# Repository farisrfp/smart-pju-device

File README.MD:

# **SMART PJU X-CAMP**

_Created by [Faris Rafi](https://www.linkedin.com/in/farisrafp/), last updated on 20 May 2023_

## **About SMART PJU**

This Smart PJU is a continuation of X-Bright with the addition of new features such as communication using LoRa, the use of new sensors, and the use of new modules. This Smart PJU also uses the concept of IoT (Internet of Things) which allows users to control this street lamp through the dashboard provided.

### **Wiring Diagram**

### **Hardware**

|               Controller V2               |
| :---------------------------------------: |
|  |

|            Power V2             |
| :-----------------------------: |
|  |

Documentation can be seen [here](./hardware/)

### **Firmware**

Here is the sensor diagram and pinout used on Controller V2.

Documentation can be seen [here](./firmware/)

## **Contact**

If you have any questions, please contact Faris, the product's designer, by E-mail.

Email : farisrafp@gmail.com

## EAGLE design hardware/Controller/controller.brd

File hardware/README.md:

# **Hardware Documentation**

## **BOM**

The BoM (Bill of Material) for this project can be seen in the table below.

### **Power Board**

| Designator | Quantity | Description |
| :--------: | :------: | :---------: |
|   AC-DC    |    1     |  AC to DC   |
|     V1     |    1     |  Varistor   |
|     F1     |    1     | Fuse Holder |
|     F2     |    1     |  Fuse PTC   |
|    DIM     |    1     |    PC817    |
|    IC1     |    1     | ACS712-05B  |
|    IC2     |    1     |   LM358N    |
|     T1     |    1     |  ZMPT101B   |
|    SSR     |    1     |  G3MB-202P  |

**Passive Components**

| Designator | Quantity |  Package  |  Value  |
| :--------: | :------: | :-------: | :-----: |
|     Q1     |    1     |  SOT-23   | SS8550  |
|     D1     |    1     |  SOD-123  | 1N4448W |
|     D2     |    1     | DO-214AC  |   M4    |
|    LED     |    1     |   0805    |  Blue   |
|     R7     |    1     |   3296    |  100K   |
|     R1     |    1     |   0805    |   100   |
|   R2 - 3   |    2     |   0805    |   330   |
|     R4     |    1     |   0805    |   2K    |
|   R5 - 6   |    2     |   0805    |  4,7K   |
|   R8 - 9   |    2     |   0805    |  100K   |
|  R10 - 17  |    8     |   0805    |   10K   |
|  R19 - 20  |    2     | Axial-7.2 |  330K   |
|   C1 - 2   |    2     |   0805    |   1u    |
|   C3 - 4   |    2     |   0805    |  100n   |
|   C5 - 8   |    4     |   0805    |   1n    |

<br>

### **Controller Board**

| Designator | Quantity |       Description        |
| :--------: | :------: | :----------------------: |
|   ESP32    |    1     |       ESP32-WROOM        |
|  REG-3V3   |    1     |       AMS1117-3V3        |
|   RA-01H   |    1     |    AI-Thinker RA-01H     |
|   DS3231   |    1     |    RTC DS3231 Module     |
|   NEO 1    |    2     |         WS2812B          |
|   S1 - 2   |    2     |       Micro Button       |
|     S3     |    1     |        DIP Switch        |
|    PH1     |    1     | Light Dependent Resistor |

**Passive Components**

| Designator | Quantity | Package | Value |
| :--------: | :------: | :-----: | :---: |
|    LED     |    1     |  0805   |  Red  |
|   R1 - 2   |    2     |  0805   |  1K   |
|     R3     |    1     |  0805   |  2K   |
|   R4 - 6   |    3     |  0805   |  10K  |
|     C1     |    1     |  0805   | 100n  |
|     C2     |    1     |  0805   |  1u   |
|   C3 - 4   |    2     |  0805   |  10u  |
|     C6     |    1     |  2412   | 100u  |

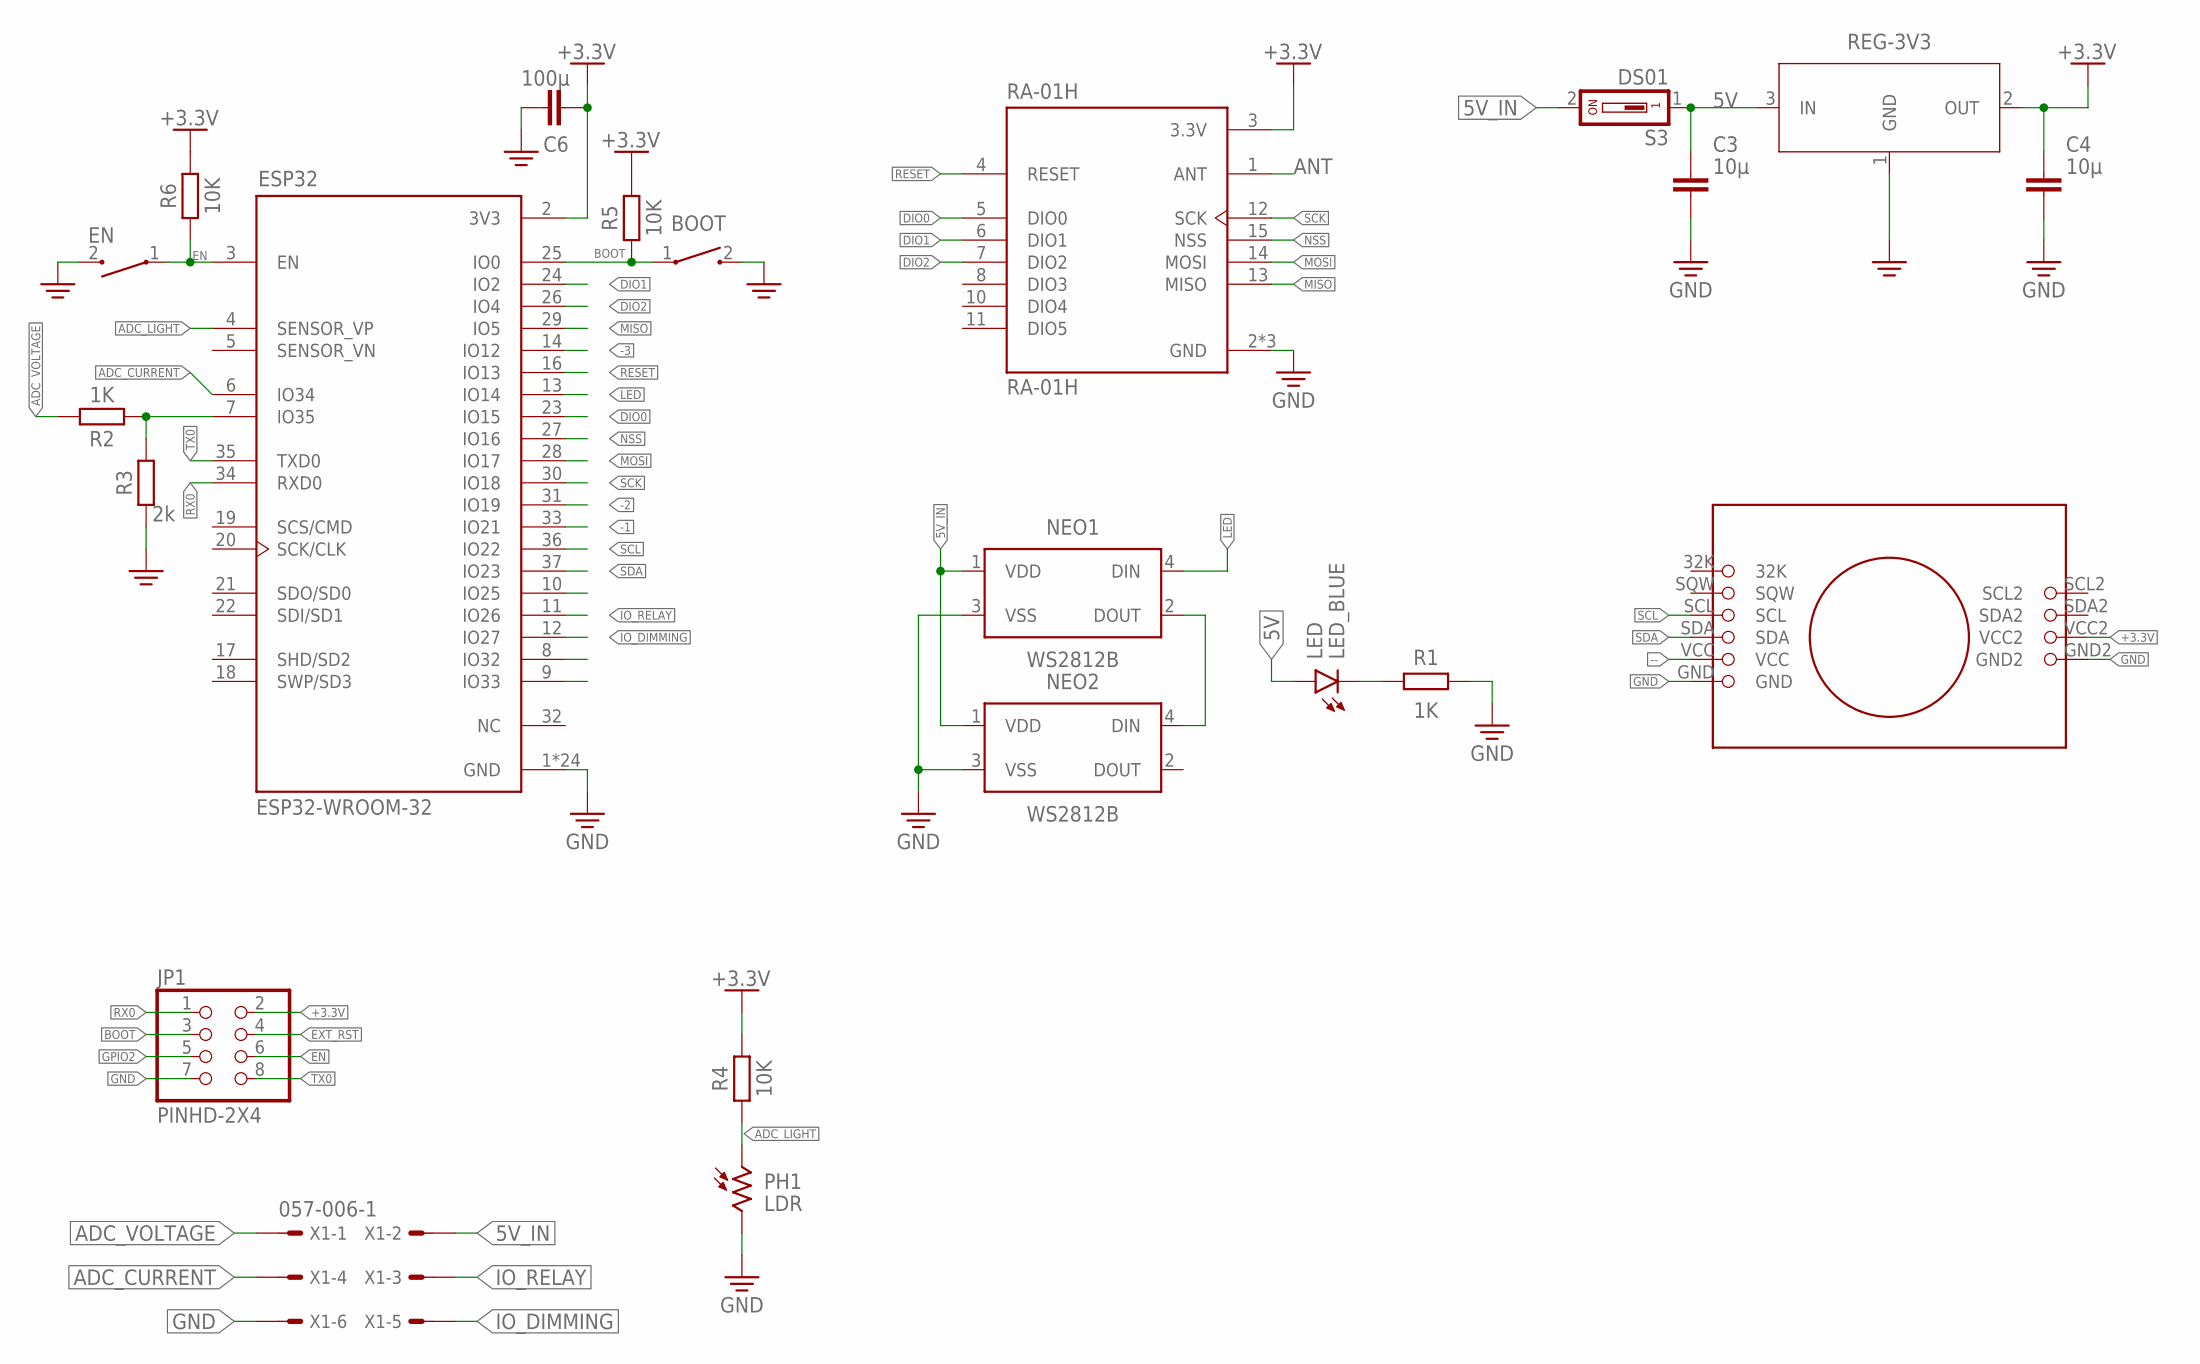
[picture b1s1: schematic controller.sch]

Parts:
BOOT: SWITCH; SW_1437566-3
C3, C4: 10µ; CAPC2012X110
C6: 100µ; CAPM6032X280
EN: SWITCH; SW_1437566-3
ESP32: ESP32-WROOM-32; MODULE_ESP32-WROOM-32
JP1: PINHD-2X4; 2X04
LED: LED_BLUE; LEDC2012X110N_FLAT-B
NEO1, NEO2: WS2812B
PH1: LDR; T0-46-A10XX
R1, R2: 1K; RESC2012X65
R3: 2k; RESC2012X65
R4: 10K; RESC1608X60
R5, R6: 10K; RESC2012X65
RA-01H: RA-01H
REG-3V3: NCP1117ST33T3G; SOT230P700X170-4
S3: DS01; DS-01
U$1: DS3231_MODULE
X1: 057-006-1

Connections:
5V: C3.1, LED.A, REG-3V3.3 (IN), S3.1
5V_IN: NEO1.1 (VDD), NEO2.1 (VDD), S3.2, X1.2
+3.3V: C4.1, C6.1, ESP32.2 (3V3), JP1.2, R4.2, R5.2, R6.2, RA-01H.3 (3.3V), REG-3V3.2 (OUT), U$1.VCC2
-1: ESP32.33 (IO21)
-2: ESP32.31 (IO19)
-3: ESP32.14 (IO12)
--: U$1.VCC
ADC_CURRENT: ESP32.6 (IO34), X1.4
ADC_LIGHT: ESP32.4 (SENSOR_VP), PH1.1, R4.1
ADC_VOLTAGE: R2.2, X1.1
ANT: RA-01H.1 (ANT)
BOOT: BOOT.1, ESP32.25 (IO0), JP1.3, R5.1
DIO0: ESP32.23 (IO15), RA-01H.5 (DIO0)
DIO1: ESP32.24 (IO2), RA-01H.6 (DIO1)
DIO2: ESP32.26 (IO4), RA-01H.7 (DIO2)
EN: EN.1, ESP32.3 (EN), JP1.6, R6.1
EXT_RST: JP1.4
GND: BOOT.2, C3.2, C4.2, C6.2, EN.2, ESP32.1 (GND), ESP32.15 (GND), ESP32.38 (GND), ESP32.39_1 (GND), ESP32.39_2 (GND), ESP32.39_3 (GND), ESP32.39_4 (GND), ESP32.39_5 (GND), ESP32.39_6 (GND), ESP32.39_7 (GND), ESP32.39_8 (GND), ESP32.39_9 (GND), ESP32.39_10 (GND), ESP32.39_11 (GND), ESP32.39_12 (GND), ESP32.39_13 (GND), ESP32.39_14 (GND), ESP32.39_15 (GND), ESP32.39_16 (GND), ESP32.39_17 (GND), ESP32.39_18 (GND), ESP32.39_19 (GND), ESP32.39_20 (GND), ESP32.39_21 (GND), JP1.7, NEO1.3 (VSS), NEO2.3 (VSS), PH1.2, R1.2, R3.1, RA-01H.2 (GND), RA-01H.9 (GND), RA-01H.16 (GND), REG-3V3.1 (GND), U$1.GND, U$1.GND2, X1.6
GPIO2: JP1.5
IO_DIMMING: ESP32.12 (IO27), X1.5
IO_RELAY: ESP32.11 (IO26), X1.3
LED: ESP32.13 (IO14), NEO1.4 (DIN)
MISO: ESP32.29 (IO5), RA-01H.13 (MISO)
MOSI: ESP32.28 (IO17), RA-01H.14 (MOSI)
unnamed: ESP32.7 (IO35), R2.1, R3.2
unnamed: NEO1.2 (DOUT), NEO2.4 (DIN)
unnamed: LED.C, R1.1
NSS: ESP32.27 (IO16), RA-01H.15 (NSS)
RESET: ESP32.16 (IO13), RA-01H.4 (RESET)
RX0: ESP32.34 (RXD0), JP1.1
SCK: ESP32.30 (IO18), RA-01H.12 (SCK)
SCL: ESP32.36 (IO22), U$1.SCL
SDA: ESP32.37 (IO23), U$1.SDA
TX0: ESP32.35 (TXD0), JP1.8

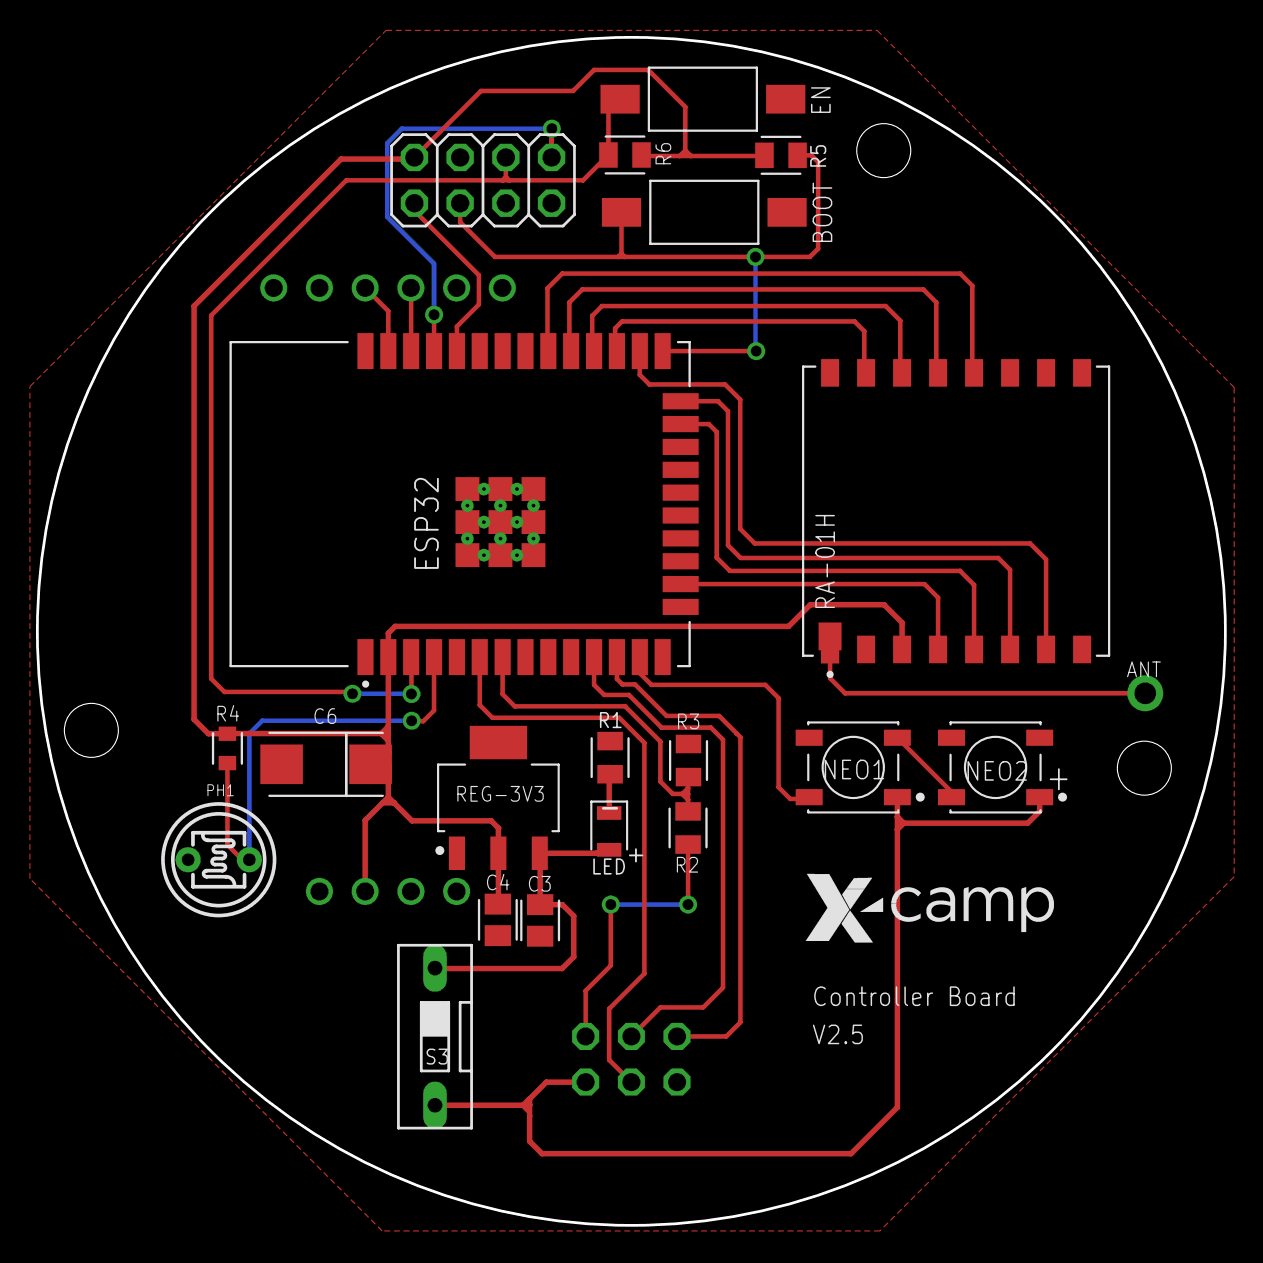
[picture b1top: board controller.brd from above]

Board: 2 copper layers, 66.0 x 66.0 mm, 22 parts (1 on the bottom side), 27 nets.

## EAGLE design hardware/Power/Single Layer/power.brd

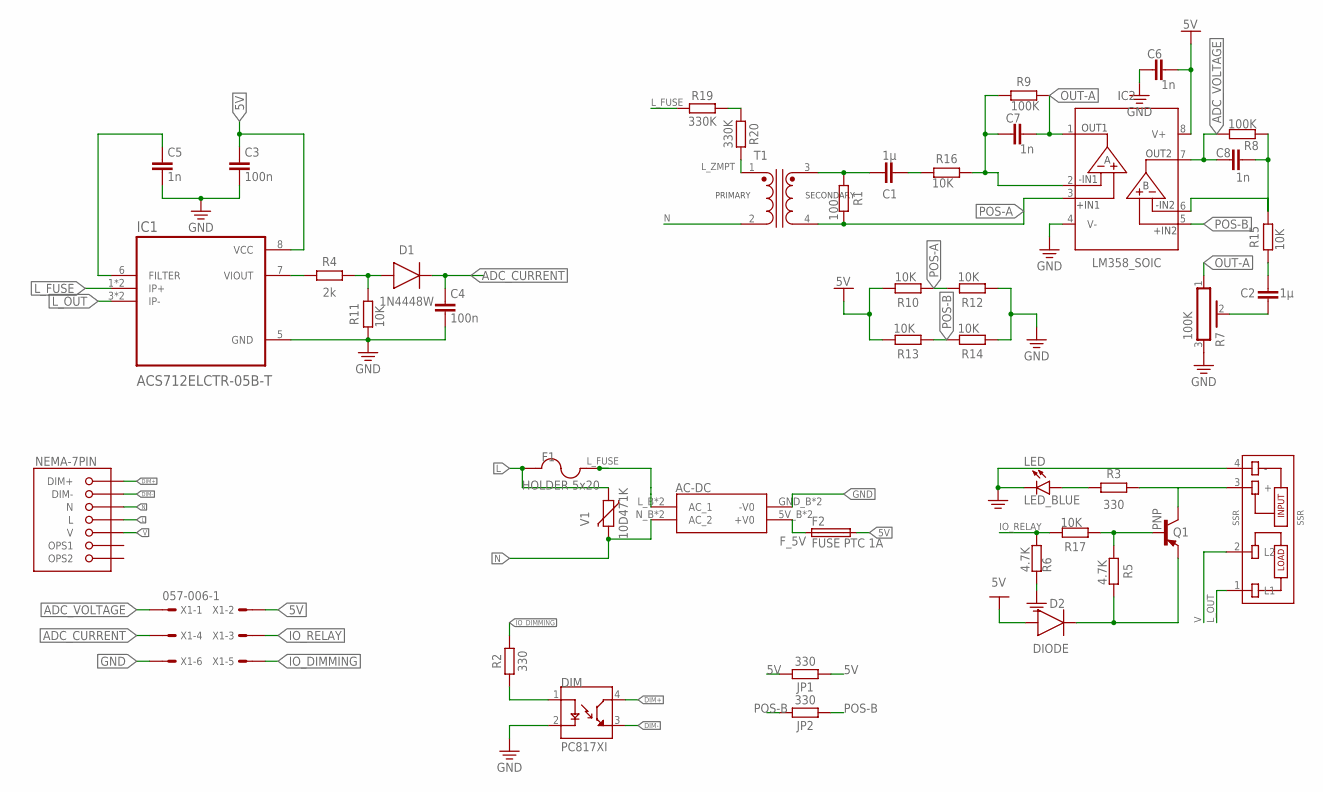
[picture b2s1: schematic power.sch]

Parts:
AC-DC: HI-LINKVERTICAL; AC-DC_3.5W(VER)
C1, C2: 1µ; CAPC2012X110
C3, C4: 100n; CAPC2012X110
C5, C6, C7, C8: 1n; CAPC2012X110
D1: 1N4448W; SOD3715X135
D2: DIODE; DIOM5226X290N
DIM: PC817XI; SOIC254P975X460-4N
F1: HOLDER 5x20; 4527
F2: FUSE PTC 1A; FUSC3215X82N
IC1: ACS712ELCTR-05B-T; SOIC127P600X175-8N@1
IC2: LM358_SOIC; SOIC127P600X175-8N
JP1, JP2: 330; RESC2012X65
LED: LED_BLUE; LEDC2012X110N_FLAT-B
NEMA-7PIN: NEMA-7P
Q1: PNP; SOT95P237X112-3N
R1: 100; RESC2012X65
R2, R3: 330; RESC2012X65
R4: 2k; RESC2012X65
R5, R6: 4.7K; RESC2012X65
R7: 100K; PV36W
R8, R9: 100K; RESC2012X65
R10, R11, R12, R13, R14, R15, R16, R17: 10K; RESC2012X65
R19, R20: 330K; RESAD724W46L381D178B
SSR: SSR; SSR_G3MB-202P
T1: ZMPT101B
V1: 10D471K; MOV-10D561
X1: 057-006-1

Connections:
5V: C3.1, C6.2, D2.2 (A), F2.2, IC1.8 (VCC), IC2.8 (V+), JP1.1, JP1.2, R10.2, R13.2, X1.2
ADC_CURRENT: C4.1, D1.1 (C), X1.4
ADC_VOLTAGE: C8.1, IC2.7 (OUT2), R8.2, X1.1
DIM+: DIM.4 (CT), NEMA-7PIN.DIM+
DIM-: DIM.3 (ET), NEMA-7PIN.DIM-
F_5V: AC-DC.5V_B (+V0), AC-DC.5V_T (+V0), F2.1
GND: AC-DC.GND_B (-V0), AC-DC.GND_T (-V0), C3.2, C4.2, C5.2, C6.1, DIM.2 (C), IC1.5 (GND), IC2.4 (V-), LED.C, R6.2, R7.3, R11.1, R12.1, R14.1, SSR.4 (-), X1.6
IO_DIMMING: R2.2, X1.5
IO_RELAY: R6.1, R17.2, X1.3
L: F1.1, NEMA-7PIN.L, V1.1
L_FUSE: AC-DC.L_B (AC_1), AC-DC.L_T (AC_1), F1.2, IC1.1 (IP+), IC1.2 (IP+), R19.1
L_OUT: IC1.3 (IP-), IC1.4 (IP-), SSR.1 (L1)
L_ZMPT: R20.2, T1.1
N: AC-DC.N_B (AC_2), AC-DC.N_T (AC_2), NEMA-7PIN.N, T1.2, V1.2
unnamed: C1.1, R1.1, T1.3
unnamed: C1.2, R16.1
unnamed: IC1.7 (VIOUT), R4.1
unnamed: R19.2, R20.1
unnamed: C7.1, IC2.2 (-IN1), R9.1, R16.2
unnamed: D1.2 (A), R4.2, R11.2
unnamed: C5.1, IC1.6 (FILTER)
unnamed: D2.1 (C), Q1.2 (E), R5.2
unnamed: Q1.1 (B), R5.1, R17.1
unnamed: Q1.3 (C), R3.2, SSR.3 (+)
unnamed: C8.2, IC2.6 (-IN2), R8.1, R15.2
unnamed: C2.2, R15.1
unnamed: C2.1, R7.2
unnamed: LED.A, R3.1
unnamed: DIM.1 (A), R2.1
OUT-A: C7.2, IC2.1 (OUT1), R7.1, R9.2
POS-A: IC2.3 (+IN1), R1.2, R10.1, R12.2, T1.4
POS-B: IC2.5 (+IN2), JP2.1, JP2.2, R13.1, R14.2
V: NEMA-7PIN.V, SSR.2 (L2)

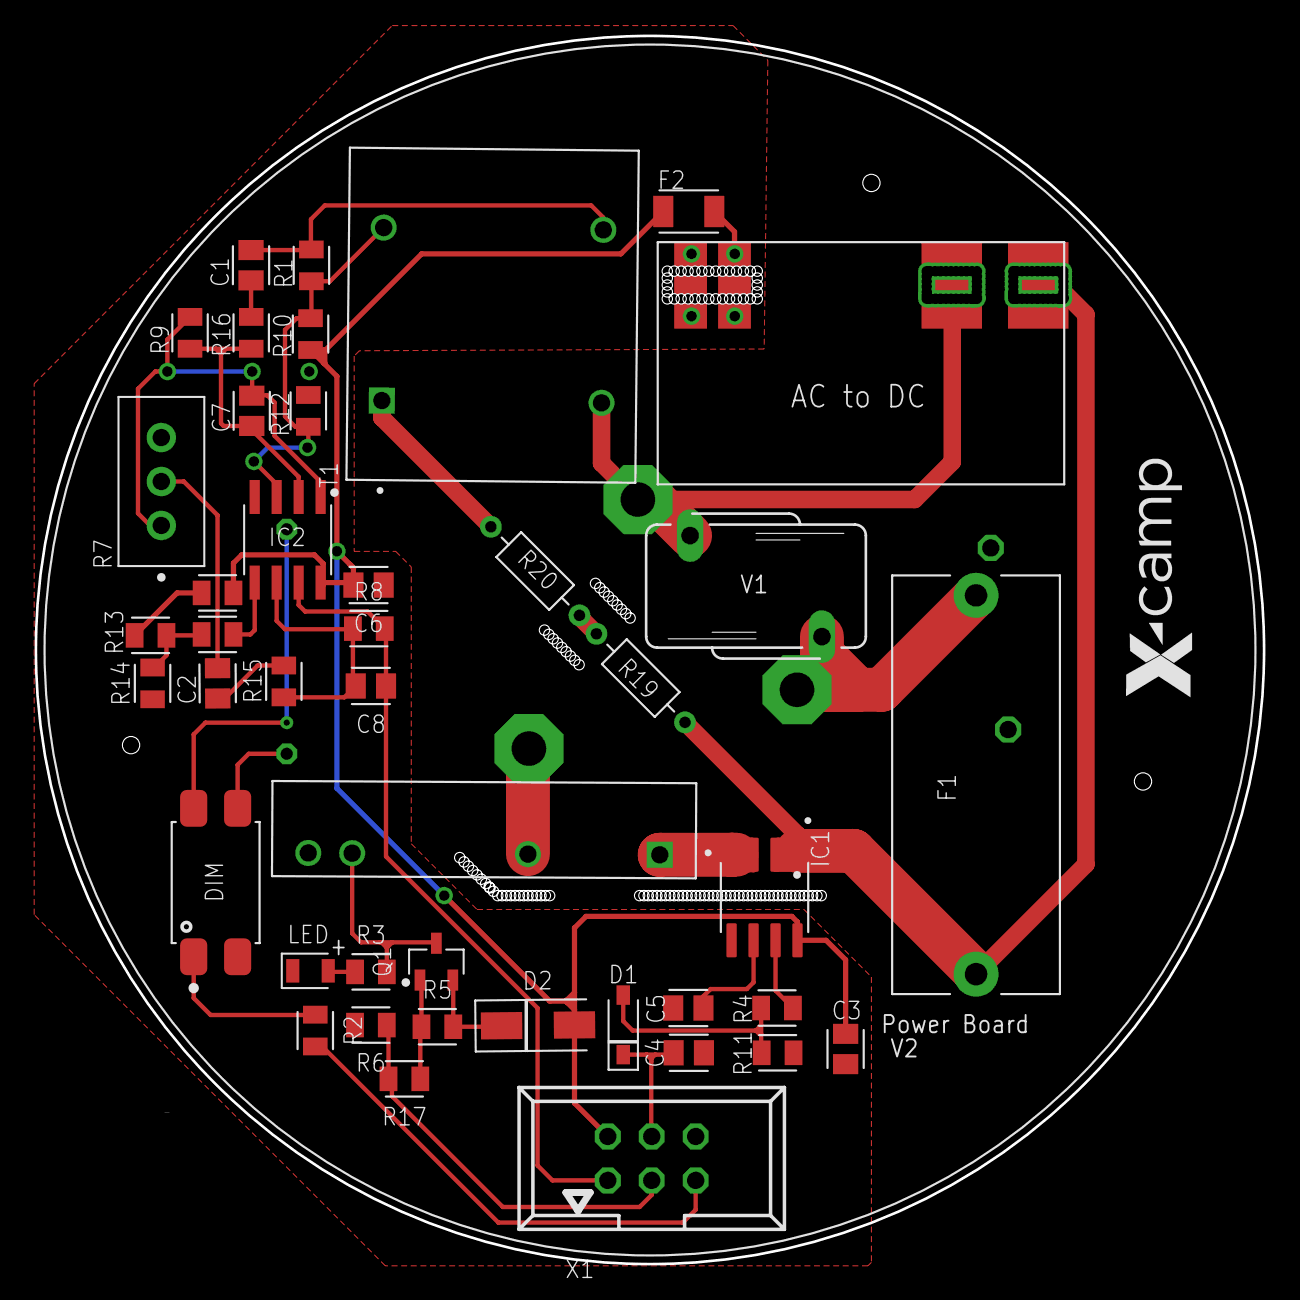
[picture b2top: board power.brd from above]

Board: 2 copper layers, 71.0 x 71.0 mm, 44 parts (0 on the bottom side), 33 nets.

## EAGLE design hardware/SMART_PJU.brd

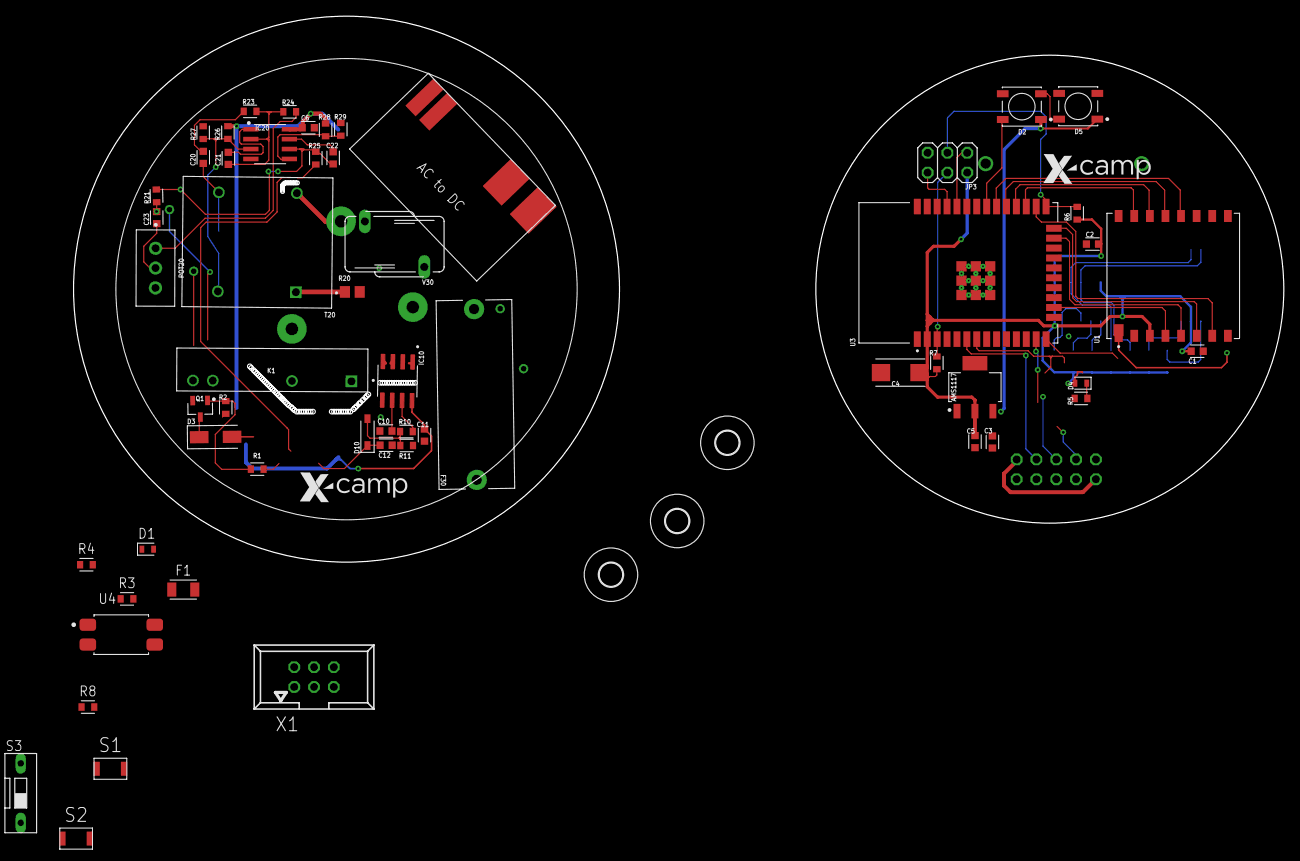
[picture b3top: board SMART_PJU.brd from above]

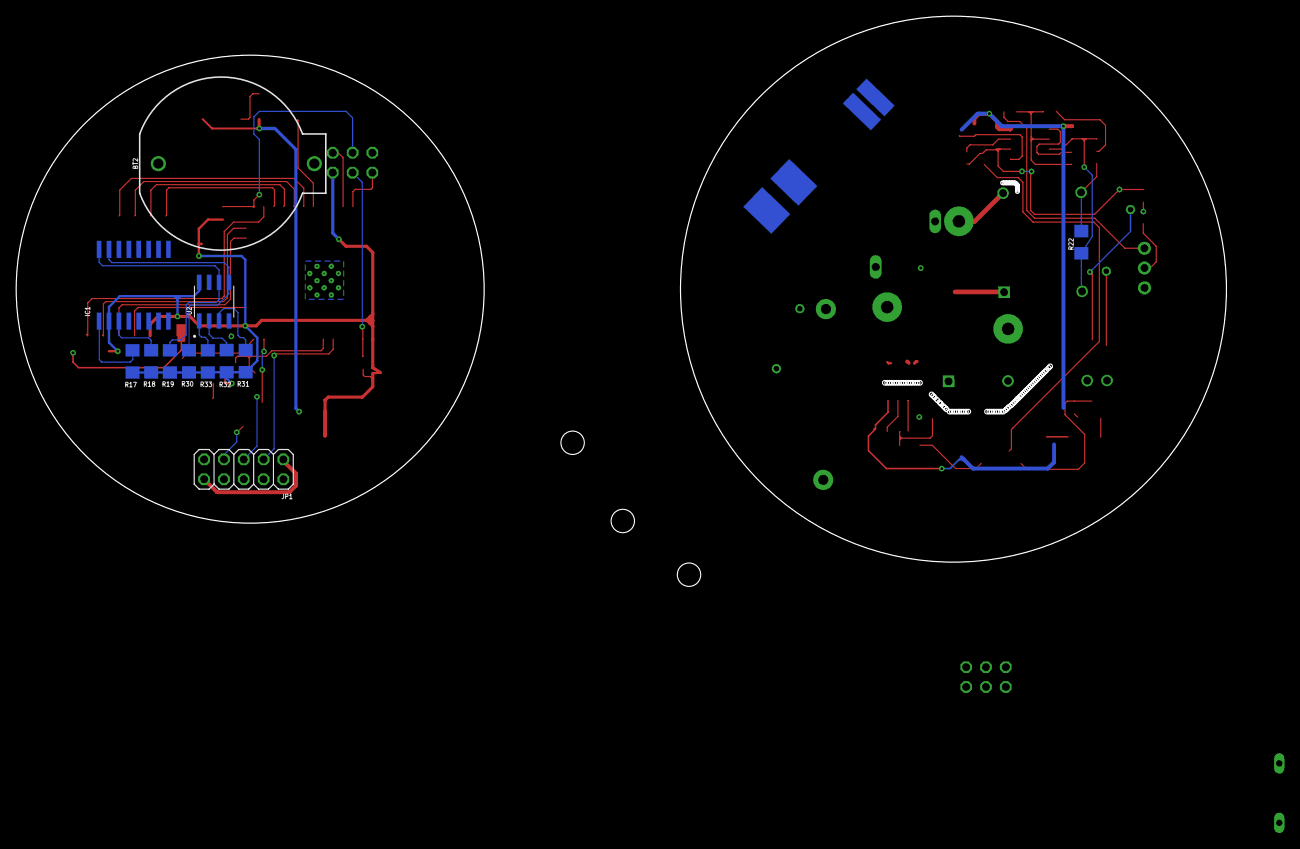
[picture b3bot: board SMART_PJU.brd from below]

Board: 2 copper layers, 155.2 x 70.0 mm, 73 parts (12 on the bottom side), 60 nets.

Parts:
AMS1117: NCP1117ST33T3G; SOT230P700X170-4
BT2: BATTCOM_20MM_PTH
C1: 1μ; CAPC1608X85
C2: 0.1μ; CAPC1608X85
C3, C5: 10µ; CAPC1608X85
C4: 100µ; CAPM6032X280
C6, C10, C21, C22: 1n; CAPC1608X85
C11, C12: 100n; CAPC1608X85
C20, C23: 1µ; CAPC1608X85
D1, D4: LED_BLUE; LEDC1608X55N_FLAT-B
D2, D5: WS2812B
D3: DIODE; DIOM5226X290N
D10: 1N4448W; SOD3715X135
F1: FUSE PTC 1A; FUSC3215X82N
F30: 4527
H1, H2, H4: HOLE3.0; 3,0
IC1: DS3231/SO; SO16W
IC10: ACS712ELCTR-05B-T; SOIC127P600X175-8N@1
IC20: LM358_SOIC; SOIC127P600X175-8N
JP1: PINHD-2X5; 2X05
JP3: PINHD-2X3; 2X03
K1: SSR; SSR_G3MB-202P
NEMA-7PIN: NEMA-7P
POT20: 10K; PV36W
PS1: HI-LINKVERTICAL; AC-DC_3.5W(VER)
Q1: PNP; SOT95P237X112-3N
R1, R6, R7, R11, R21, R23, R26, R27, R28, R29: 10k; RESC1608X60
R2, R8: 4.7k; RESC1608X60
R3, R4, R5: 330; RESC1608X60
R10: 2k; RESC1608X60
R17, R18, R19, R30, R31, R32, R33: 10k; R1206
R20: 820K; R0805
R22: 100; R1206
R24, R25: 100K; RESC1608X60
S1, S2: B3U-1000P(M)
S3: DS01; DS-01
T20: ZMPT101B
U1: RA-01H
U2: AT24C64N-10SC; SOIC127P600X175-8N
U3: ESP32-WROOM-32; MODULE_ESP32-WROOM-32
U4: PC817XI; SOIC254P975X460-4N
V30: 10D471K; MOV-10D561
X1: 057-006-1

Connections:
5V: C6.2, C11.1, D2.1, D3.2, D4.A, D5.1, F1.2, IC10.8, IC20.8, JP1.1, JP1.10, R26.2, R28.2, S3.2, X1.2
+3.3V: AMS1117.2, C1.1, C2.1, C4.1, C5.1, IC1.2, JP3.2, R6.2, R7.2, R17.1, R18.1, R19.1, R30.1, R31.2, R32.2, R33.2, U1.3, U2.8, U3.2
ADC_CURRENT: C12.1, D10.1, JP1.3, U3.6, X1.3
ADC_VOLTAGE: JP1.5, R25.2, U3.7, X1.1
BOOT: JP3.3, R6.1, S2.1, U3.25
DIM+: NEMA-7PIN.DIM-, U4.4
DIM-: NEMA-7PIN.DIM+, U4.3
DIO0: U1.5, U3.23
DIO1: U1.6, U3.24
DIO2: U1.7, U3.26
EN: JP3.4, R7.1, S1.1, U3.3
GND: C1.2, C3.2, C4.2, C5.2, C6.1, C10.2, C11.2, C12.2, D1.C, D2.3, D5.3, IC1.13, IC10.5, IC20.4, JP1.2, JP1.9, JP3.5, K1.4, POT20.3, PS1.GND_B, PS1.GND_T, R5.2, R11.1, R27.1, R29.1, S1.2, S2.2, U1.2, U1.9, U1.16, U2.4, U2.7, U3.1, U3.15, U3.38, U3.39_1, U3.39_2, U3.39_3, U3.39_4, U3.39_5, U3.39_6, U3.39_7, U3.39_8, U3.39_9, U3.39_10, U3.39_11, U3.39_12, U3.39_13, U3.39_14, U3.39_15, U3.39_16, U3.39_17, U3.39_18, U3.39_19, U3.39_20, U3.39_21, U4.2, X1.5
IO_RELAY: JP1.7, R1.2, R8.1, U3.13, X1.4
L: F30.1, NEMA-7PIN.L
LED: D2.4, U3.31
L_FUSE: F30.2, IC10.1, IC10.2, PS1.L_B, PS1.L_T, R20.2, V30.1
L_OUT: IC10.3, IC10.4, K1.1
L_ZMPT: R20.1, T20.1
MISO: U1.13, U3.29
MOSI: U1.14, U3.28
N: NEMA-7PIN.N, PS1.N_B, PS1.N_T, T20.2, V30.2
unnamed: C20.1, R22.1, T20.3
unnamed: C21.2, IC20.1
unnamed: C20.2, R23.1
unnamed: IC10.7, R10.1
unnamed: R33.1, U2.1
unnamed: R32.1, U2.2
unnamed: C22.1, IC20.7
unnamed: C21.1, IC20.2, R23.2, R24.1
unnamed: D10.2, R10.2, R11.2
unnamed: R31.1, U2.3
unnamed: C10.1, IC10.6
unnamed: D3.1, Q1.2, R2.2
unnamed: Q1.1, R1.1, R2.1
unnamed: D2.2, D5.4
unnamed: K1.3, Q1.3, R3.2
unnamed: C22.2, IC20.6, R21.2, R25.1
unnamed: C23.2, R21.1
unnamed: C23.1, POT20.2
unnamed: BT2.1, IC1.14
unnamed: IC1.3, R18.2
unnamed: IC1.1, R17.2
unnamed: F1.1, PS1.5V_B, PS1.5V_T
unnamed: BT2.2, C2.2
unnamed: D1.A, R3.1
unnamed: D4.C, R5.1
unnamed: AMS1117.3, C3.1, S3.1
unnamed: R4.1, U4.1
NSS: U1.15, U3.27
OUT-A: POT20.1, R24.2
POS-A: IC20.3, R22.2, R26.1, R27.2, T20.4
POS-B: IC20.5, R28.1, R29.2
PWM_DIM: R4.2, U3.14
RESET: U1.4, U3.16
RX0: JP3.1, U3.34
SCK: U1.12, U3.30
SCL: IC1.16, R19.2, U2.6, U3.36
SDA: IC1.15, R30.2, U2.5, U3.33
TX0: JP3.6, U3.35
V: K1.2, NEMA-7PIN.V

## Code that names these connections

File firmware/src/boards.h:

#ifndef BOARDS_H
#define BOARDS_H

#include <ACS712.h>
#include <Arduino.h>
#include <EEPROM.h>
#include <FastLED.h>
#include <RTClib.h>
#include <SPI.h>
#include <Wire.h>
#include <ZMPT101B.h>

// Calibration Data
#define ACS712_ZP 2400
#define VOLTAGE_SENSITIVITY 1200.0f

// EEPROM Address
#define EEPROM_SIZE 512
#define ADDR_CURRENT 0
#define ADDR_VOLTAGE 2
#define ADDR_APPEUI 4
#define ADDR_DEVEUI 12
#define ADDR_APPKEY 20

// Debug printing
#define DEBUG_PORT Serial
#if defined(VERBOSE)
#define DEBUG_PRINTF(...) \
    { DEBUG_PORT.printf(__VA_ARGS__); }
#define DEBUG_PRINTF_TS(...)                                    \
    {                                                           \
        DEBUG_PORT.printf("%d ms: ", osticks2ms(os_getTime())); \
        DEBUG_PORT.printf(__VA_ARGS__);                         \
    }
#else
#define DEBUG_PRINTF(...) \
    {}
#define DEBUG_PRINTF_TS(...) \
    {}
#endif

#include "AP/webserver.h"
#include "LED/led.h"
#include "LoRaWAN/loramac.h"
#include "Sensor/sensor.h"

/* Function */
void initBoard();

/* Pin Mapping */
#define UNUSE_PIN (0)

#ifdef PROTOTYPE

#define I2C_SDA 23
#define I2C_SCL 22

#define SPI_SCLK 5
#define SPI_MISO 19
#define SPI_MOSI 27
#define PIN_NSS 18
#define PIN_RST 23
#define PIN_DIO0 26
#define PIN_DIO1 33
#define PIN_DIO2 32

// Other
#define WS2812B_PIN 14
#define RELAY_PIN 15
#define DIMMER_PIN 13
#define ADC_CURRENT 34
#define ADC_VOLTAGE 35
#define ADC_LIGHT 36
#define LED_BOARD 25

#else

#define I2C_SDA 23
#define I2C_SCL 22

#define SPI_SCLK 18
#define SPI_MISO 5
#define SPI_MOSI 17
#define PIN_NSS 16
#define PIN_RST 13
#define PIN_DIO0 15
#define PIN_DIO1 2
#define PIN_DIO2 4
// Other
#define WS2812B_PIN 14
#define RELAY_PIN 26
#define DIMMER_PIN 27
#define ADC_CURRENT 34
#define ADC_VOLTAGE 35
#define ADC_LIGHT 36
#define LED_BOARD 2

#endif

#endif

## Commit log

2023-03-19 feat : lorawan
2023-03-19 refactor : organize file and folder
2023-03-19 feat : sensor, access point done
2023-03-22 feat : led indicator
2023-03-22 feat : freeRTOS on led
2023-03-23 fix : benerin led fade dan blink
2023-04-02 lilygo succes
2023-04-26 include hardware
2023-04-26 fix : readme structure
2023-04-28 doc : README.md
2023-05-09 failed arduino lorawan
2023-05-10 feat : checkpoint 10 mei
2023-05-12 update firmware
2023-05-12 update hardware
2023-05-12 schematic change
2023-05-12 checkpoint controller
2023-05-14 bakcup before ganti ukuran smd
2023-05-14 checkpoint sebelum cetak single layer
2023-05-16 feat : checkpoint 2
2023-05-16 readme error
2023-05-16 edit readme
2023-05-19 Merge commit 'ad2010fd0a1d412e2901b50e6cc7a45f280bb39c' into dev
    # Conflicts:
    # README.MD
    # README.md
    # REAME.md
2023-05-19 fix : 2 layer pcb, dim pin terhalang
2023-05-20 readme
2023-05-21 checkpoint 21/05
2023-05-26 feat : react to esp32 script
2023-05-29 checkpoint: interface
2023-05-30 feat : checkpoint for interface dev 👾
2023-06-04 fix : dim control, lora message decoder 🎐
2023-06-04 pinddah
2023-06-05 feat : preferences new lib 🆕
2023-06-05 new update
2023-06-05 for test 🧪
2023-06-05 fix : error lmic
2023-06-05 fix : error
2023-06-07 dev : web interface
2023-06-07 fix : typescript error, rollback to js
2023-06-10 feat : firmware updated
2023-06-11 feat : EEPROM 💿
2023-06-12 fix : versi stable

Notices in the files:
parts and their libraries:
SparkFun-Batteries: Licensing: Creative Commons ShareAlike 4.0 International - https://creativecommons.org/licenses/by-sa/4.0
